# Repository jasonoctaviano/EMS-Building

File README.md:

# EMS-Building
Energy monitoring system for house or building using mbed

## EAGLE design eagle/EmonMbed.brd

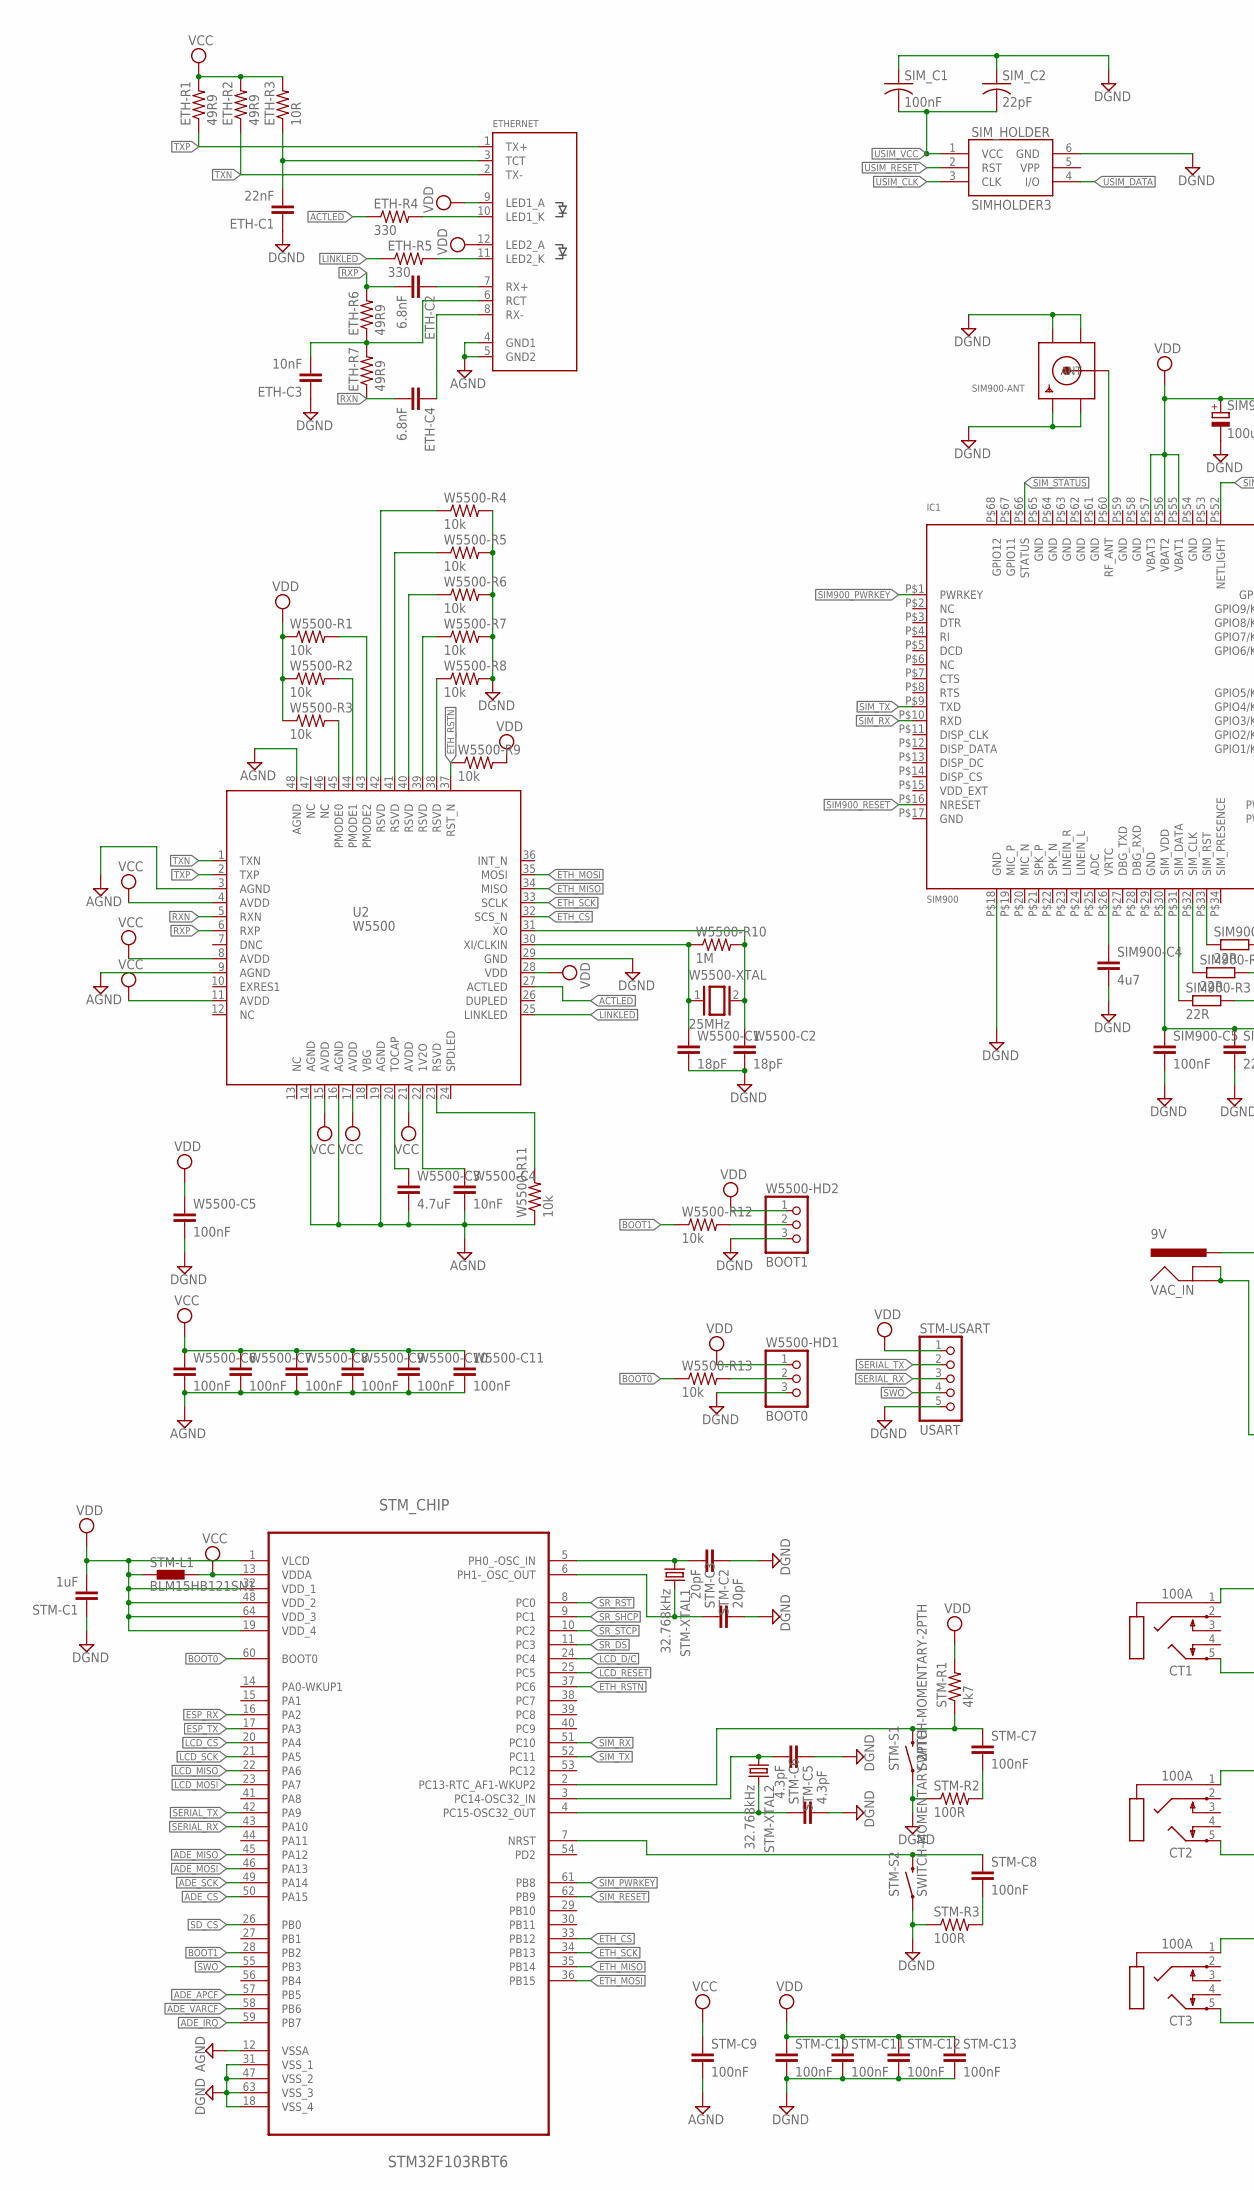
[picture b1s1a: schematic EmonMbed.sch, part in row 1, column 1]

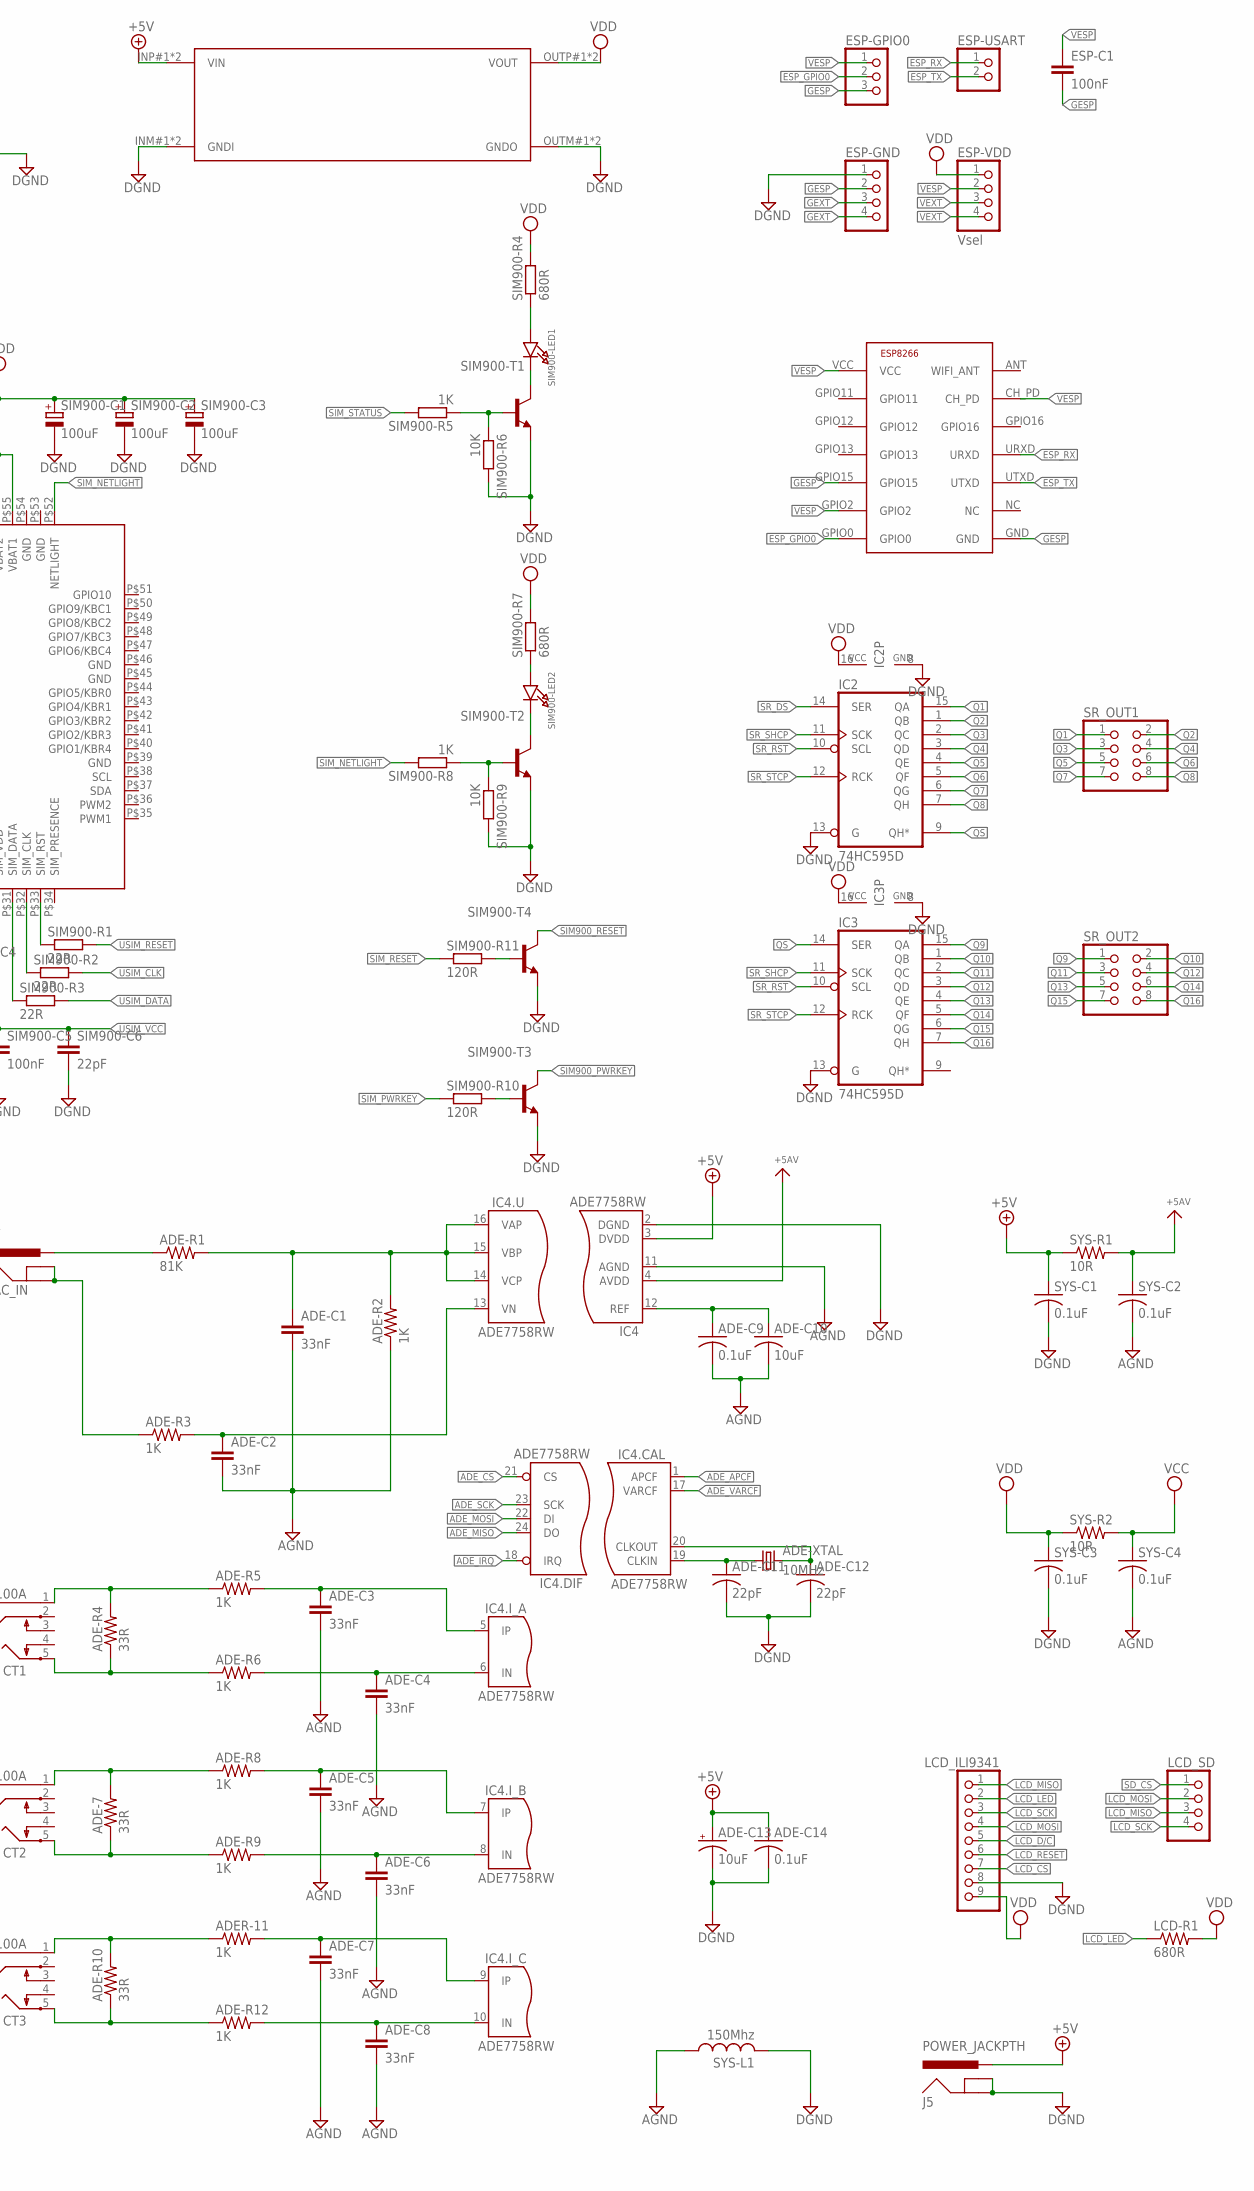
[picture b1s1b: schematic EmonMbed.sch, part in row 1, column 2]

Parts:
ADE-7: 33R; 0603-RES
ADE-C1, ADE-C2, ADE-C3, ADE-C4, ADE-C5, ADE-C6, ADE-C7, ADE-C8: 33nF; 0603-CAP
ADE-C9: 0.1uF; C0805K
ADE-C10: 10uF; C0805K
ADE-C11, ADE-C12: 22pF; C0805K
ADE-C13: 10uF; C/6032-28R
ADE-C14: 0.1uF; C0805
ADE-R1: 81K; 0603-RES
ADE-R2, ADE-R3, ADE-R5, ADE-R6, ADE-R8, ADE-R9, ADE-R12: 1K; 0603-RES
ADE-R4, ADE-R10: 33R; 0603-RES
ADE-XTAL: 10MHz; HC49US
ADER-11: 1K; 0603-RES
CT1, CT2, CT3: 100A; STX3100
DCDC-3.5V: DCDCMODULE_SMALL; DCDCMODULE-SMALL
ESP8266: ESP-07
ESP-C1: 100nF; C0603
ESP-GND: PINHD-1X4; 1X04
ESP-GPIO0: PINHD-1X3; 1X03
ESP-USART: PINHD-1X2; 1X02
ESP-VDD: Vsel; 1X04
ETH-C1: 22nF; C0603
ETH-C2, ETH-C4: 6.8nF; C0603
ETH-C3: 10nF; C0603
ETH-R1, ETH-R2, ETH-R6, ETH-R7: 49R9; R0603
ETH-R3: 10R; R0603
ETH-R4, ETH-R5: 330; R0603
ETHERNET: RJ45J0026D21BNL; RJ45_PULSEJACK
IC1: SIM900; SIM900_SMT
IC2, IC3: 74HC595D; SO16
IC4: ADE7758RW; SOIC24
J5: POWER_JACKPTH; POWER_JACK_PTH
LCD-R1: 680R; 0603-RES
LCD_ILI9341: PINHD-1X9; 1X09
LCD_SD: PINHD-1X4; 1X04
SIM900-ANT: SMACONNECTOR; SMA90_DIP
SIM900-C1, SIM900-C2, SIM900-C3: 100uF; 153CLV-0605
SIM900-C4: 4u7; C0603
SIM900-C5: 100nF; C0603
SIM900-C6: 22pF; C0603
SIM900-LED1, SIM900-LED2: LED0805_NOOUTLINE; CHIPLED_0805_NOOUTLINE
SIM900-R1, SIM900-R2, SIM900-R3: 22R; R0603
SIM900-R4, SIM900-R7: 680R; R0603
SIM900-R5, SIM900-R8: 1K; R0603
SIM900-R6, SIM900-R9: 10K; R0603
SIM900-R10, SIM900-R11: 120R; R0603
SIM900-T1, SIM900-T2, SIM900-T3, SIM900-T4: MMBT2222ALT1-NPN-SOT23-BEC; SOT23-BEC
SIM_C1: 100nF; C0603K
SIM_C2: 22pF; C0603K
SIM_HOLDER: SIMHOLDER3
SR_OUT1, SR_OUT2: PINHD-2X4/90; 2X04/90
STM-C1: 1uF; C0603
STM-C2, STM-C3: 20pF; C0603
STM-C5, STM-C6: 4.3pF; C0603
STM-C7, STM-C8, STM-C9, STM-C10, STM-C11, STM-C12, STM-C13: 100nF; C0603
STM-L1: BLM15HB121SN1; 0402
STM-R1: 4k7; R0603
STM-R2, STM-R3: 100R; R0603
STM-S1, STM-S2: SWITCH-MOMENTARY-2PTH; TACTILE-PTH
STM-USART: USART; 1X05
STM-XTAL1, STM-XTAL2: 32.768kHz; TC26H
STM_CHIP: STM32F103RBT6; QFP50P1200X1200X160-64N
SYS-C1, SYS-C2, SYS-C3, SYS-C4: 0.1uF; C0805
SYS-L1: 150Mhz; POWER-CHOKE_WE-TPC
SYS-R1, SYS-R2: 10R; 0603-RES
U2: W5500
VAC_IN: 9V; POWER_JACK_PTH
W5500-C1, W5500-C2: 18pF; C0603
W5500-C3: 4.7uF; C0603
W5500-C4: 10nF; C0603
W5500-C5, W5500-C6, W5500-C7, W5500-C8, W5500-C9, W5500-C10, W5500-C11: 100nF; C0603
W5500-HD1: BOOT0; 1X03
W5500-HD2: BOOT1; 1X03
W5500-R1, W5500-R2, W5500-R3, W5500-R4, W5500-R5, W5500-R6, W5500-R7, W5500-R8, W5500-R9, W5500-R11, W5500-R12, W5500-R13: 10k; R0603
W5500-R10: 1M; R0603
W5500-XTAL: 25MHz; QS

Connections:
+5V: ADE-C13.+, ADE-C14.1, DCDC-3.5V.INP#1 (VIN), DCDC-3.5V.INP#2 (VIN), IC4.3 (DVDD), J5.PWR, SYS-C1.1, SYS-R1.1
ACTLED: ETH-R4.1, U2.27 (ACTLED)
ADE_APCF: IC4.1 (APCF), STM_CHIP.57 (PB5)
ADE_CS: IC4.21 (CS), STM_CHIP.50 (PA15)
ADE_IRQ: IC4.18 (IRQ), STM_CHIP.59 (PB7)
ADE_MISO: IC4.24 (DO), STM_CHIP.45 (PA12)
ADE_MOSI: IC4.22 (DI), STM_CHIP.46 (PA13)
ADE_SCK: IC4.23 (SCK), STM_CHIP.49 (PA14)
ADE_VARCF: IC4.17 (VARCF), STM_CHIP.58 (PB6)
AGND: ADE-C1.2, ADE-C2.2, ADE-C3.2, ADE-C4.2, ADE-C5.2, ADE-C6.2, ADE-C7.2, ADE-C8.2, ADE-C9.2, ADE-C10.2, ADE-R2.1, ETHERNET.4 (GND1), ETHERNET.5 (GND2), IC4.11 (AGND), STM-C9.2, STM_CHIP.12 (VSSA), SYS-C2.2, SYS-C4.2, SYS-L1.1, U2.3 (AGND), U2.9 (AGND), U2.14 (AGND), U2.16 (AGND), U2.19 (AGND), U2.48 (AGND), W5500-C3.2, W5500-C4.2, W5500-C6.2, W5500-C7.2, W5500-C8.2, W5500-C9.2, W5500-C10.2, W5500-C11.2, W5500-R11.1
AVDD: IC4.4 (AVDD), SYS-C2.1, SYS-R1.2
BOOT0: STM_CHIP.60 (BOOT0), W5500-R13.1
BOOT1: STM_CHIP.28 (PB2), W5500-R12.1
DGND: ADE-C11.2, ADE-C12.2, ADE-C13.-, ADE-C14.2, DCDC-3.5V.INM#1 (GNDI), DCDC-3.5V.INM#2 (GNDI), DCDC-3.5V.OUTM#1 (GNDO), DCDC-3.5V.OUTM#2 (GNDO), ESP-GND.1, ETH-C1.1, ETH-C3.1, IC1.P$18 (GND), IC2.8 (GND), IC2.13 (G), IC3.8 (GND), IC3.13 (G), IC4.2 (DGND), J5.GND, J5.GNDBREAK, LCD_ILI9341.8, SIM900-ANT.GND1, SIM900-ANT.GND2, SIM900-ANT.GND3, SIM900-ANT.GND4, SIM900-C1.-, SIM900-C2.-, SIM900-C3.-, SIM900-C4.2, SIM900-C5.2, SIM900-C6.2, SIM900-R6.2, SIM900-R9.2, SIM900-T1.E, SIM900-T2.E, SIM900-T3.E, SIM900-T4.E, SIM_C1.1, SIM_C2.1, SIM_HOLDER.6 (GND), STM-C1.1, STM-C2.1, STM-C3.2, STM-C5.1, STM-C6.2, STM-C10.2, STM-C11.2, STM-C12.2, STM-C13.2, STM-R2.1, STM-R3.1, STM-S1.1, STM-S2.1, STM-USART.5, STM_CHIP.18 (VSS_4), STM_CHIP.31 (VSS_1), STM_CHIP.47 (VSS_2), STM_CHIP.63 (VSS_3), SYS-C1.2, SYS-C3.2, SYS-L1.2, U2.29 (GND), W5500-C1.2, W5500-C2.2, W5500-C5.2, W5500-HD1.3, W5500-HD2.3, W5500-R4.2, W5500-R5.2, W5500-R6.2, W5500-R7.2, W5500-R8.2
ESP_GPIO0: ESP8266.GPIO0, ESP-GPIO0.2
ESP_RX: ESP8266.URXD, ESP-USART.1, STM_CHIP.16 (PA2)
ESP_TX: ESP8266.UTXD, ESP-USART.2, STM_CHIP.17 (PA3)
ETH_CS: STM_CHIP.33 (PB12), U2.32 (SCS_N)
ETH_MISO: STM_CHIP.35 (PB14), U2.34 (MISO)
ETH_MOSI: STM_CHIP.36 (PB15), U2.35 (MOSI)
ETH_RSTN: STM_CHIP.37 (PC6), U2.37 (RST_N), W5500-R9.1
ETH_SCK: STM_CHIP.34 (PB13), U2.33 (SCLK)
GESP: ESP8266.GND, ESP8266.GPIO15, ESP-C1.2, ESP-GND.2, ESP-GPIO0.3
GEXT: ESP-GND.3, ESP-GND.4
GND: IC1.P$17 (GND), IC1.P$29 (GND), IC1.P$39 (GND), IC1.P$45 (GND), IC1.P$46 (GND), IC1.P$53 (GND), IC1.P$54 (GND), IC1.P$58 (GND), IC1.P$59 (GND), IC1.P$61 (GND), IC1.P$62 (GND), IC1.P$63 (GND), IC1.P$64 (GND), IC1.P$65 (GND)
GPIO11: IC1.P$67 (GPIO11)
GPIO12: IC1.P$68 (GPIO12)
IBN: ADE-7.1, ADE-R9.1, CT2.5
ICN: ADE-R10.1, ADE-R12.1, CT3.5
LCD_CS: LCD_ILI9341.7, STM_CHIP.20 (PA4)
LCD_D/C: LCD_ILI9341.5, STM_CHIP.24 (PC4)
LCD_LED: LCD-R1.1, LCD_ILI9341.2
LCD_MISO: LCD_ILI9341.1, LCD_SD.3, STM_CHIP.22 (PA6)
LCD_MOSI: LCD_ILI9341.4, LCD_SD.2, STM_CHIP.23 (PA7)
LCD_RESET: LCD_ILI9341.6, STM_CHIP.25 (PC5)
LCD_SCK: LCD_ILI9341.3, LCD_SD.4, STM_CHIP.21 (PA5)
LINKLED: ETH-R5.1, U2.25 (LINKLED)
unnamed: STM-C5.2, STM-XTAL2.1, STM_CHIP.3 (PC14-OSC32_IN)
unnamed: STM-C6.1, STM-XTAL2.2, STM_CHIP.4 (PC15-OSC32_OUT)
unnamed: IC1.P$31 (SIM_DATA), SIM900-R3.1
unnamed: STM-C7.1, STM-R1.1, STM-S1.3 (2), STM_CHIP.2 (PC13-RTC_AF1-WKUP2)
unnamed: STM-C7.2, STM-R2.2
unnamed: STM-C2.2, STM-XTAL1.1, STM_CHIP.5 (PH0_-OSC_IN)
unnamed: STM-C3.1, STM-XTAL1.2, STM_CHIP.6 (PH1-_OSC_OUT)
unnamed: IC1.P$32 (SIM_CLK), SIM900-R2.1
unnamed: STM-C8.2, STM-R3.2
unnamed: ETH-R4.2, ETHERNET.10 (LED1_K)
unnamed: ETH-R5.2, ETHERNET.11 (LED2_K)
unnamed: IC1.P$33 (SIM_RST), SIM900-R1.1
unnamed: IC1.P$26 (VRTC), SIM900-C4.1
unnamed: IC1.P$60 (RF_ANT), SIM900-ANT.ANTENNA (ANT)
unnamed: SIM900-LED1.A, SIM900-R4.1
unnamed: SIM900-LED1.C, SIM900-T1.C
unnamed: SIM900-R5.1, SIM900-R6.1, SIM900-T1.B
unnamed: SIM900-LED2.A, SIM900-R7.1
unnamed: SIM900-LED2.C, SIM900-T2.C
unnamed: SIM900-R8.1, SIM900-R9.1, SIM900-T2.B
unnamed: ETH-C2.1, ETHERNET.7 (RX+)
unnamed: ETH-C1.2, ETH-R3.1, ETHERNET.3 (TCT)
unnamed: ADE-C7.1, ADER-11.2, IC4.9 (IP)
unnamed: ADE-7.2, ADE-R8.1, CT2.1
unnamed: ETH-C4.1, ETHERNET.8 (RX-)
unnamed: ADE-C3.1, ADE-R5.2, IC4.5 (IP)
unnamed: ADE-C4.1, ADE-R6.2, IC4.6 (IN)
unnamed: ETH-C3.2, ETH-R6.1, ETH-R7.2, ETHERNET.6 (RCT)
unnamed: ADE-C6.1, ADE-R9.2, IC4.8 (IN)
unnamed: ADE-C5.1, ADE-R8.2, IC4.7 (IP)
unnamed: ADE-C9.1, ADE-C10.1, IC4.12 (REF)
unnamed: ADE-C11.1, ADE-XTAL.1, IC4.19 (CLKIN)
unnamed: ADE-C12.1, ADE-XTAL.2, IC4.20 (CLKOUT)
unnamed: ADE-C2.1, ADE-R3.2, IC4.13 (VN)
unnamed: ADE-R1.1, VAC_IN.PWR
unnamed: ADE-C1.1, ADE-R1.2, ADE-R2.2, IC4.14 (VCP), IC4.15 (VBP), IC4.16 (VAP)
unnamed: U2.20 (TOCAP), W5500-C3.1
unnamed: ADE-R4.2, ADE-R5.1, CT1.1
unnamed: ADE-C8.1, ADE-R12.2, IC4.10 (IN)
unnamed: U2.22 (1V2O), W5500-C4.1
unnamed: U2.23 (RSVD), W5500-R11.2
unnamed: W5500-HD1.2, W5500-R13.2
unnamed: SIM900-R10.2, SIM900-T3.B
unnamed: SIM900-R11.2, SIM900-T4.B
unnamed: W5500-HD2.2, W5500-R12.2
unnamed: ADE-R4.1, ADE-R6.1, CT1.5
unnamed: ADE-R10.2, ADER-11.1, CT3.1
unnamed: U2.30 (XI/CLKIN), W5500-C1.1, W5500-R10.1, W5500-XTAL.1
unnamed: U2.31 (XO), W5500-C2.1, W5500-R10.2, W5500-XTAL.2
unnamed: ADE-R3.1, VAC_IN.GND, VAC_IN.GNDBREAK
unnamed: U2.38 (RSVD), W5500-R8.1
unnamed: U2.39 (RSVD), W5500-R7.1
unnamed: U2.40 (RSVD), W5500-R6.1
unnamed: U2.41 (RSVD), W5500-R5.1
unnamed: U2.42 (RSVD), W5500-R4.1
unnamed: U2.43 (PMODE2), W5500-R1.2
unnamed: U2.44 (PMODE1), W5500-R2.2
unnamed: U2.45 (PMODE0), W5500-R3.2
NRST: STM-C8.1, STM-S2.3 (2), STM_CHIP.7 (NRST)
Q1: IC2.15 (QA), SR_OUT1.1
Q2: IC2.1 (QB), SR_OUT1.2
Q3: IC2.2 (QC), SR_OUT1.3
Q4: IC2.3 (QD), SR_OUT1.4
Q5: IC2.4 (QE), SR_OUT1.5
Q6: IC2.5 (QF), SR_OUT1.6
Q7: IC2.6 (QG), SR_OUT1.7
Q8: IC2.7 (QH), SR_OUT1.8
Q9: IC3.15 (QA), SR_OUT2.1
Q10: IC3.1 (QB), SR_OUT2.2
Q11: IC3.2 (QC), SR_OUT2.3
Q12: IC3.3 (QD), SR_OUT2.4
Q13: IC3.4 (QE), SR_OUT2.5
Q14: IC3.5 (QF), SR_OUT2.6
Q15: IC3.6 (QG), SR_OUT2.7
Q16: IC3.7 (QH), SR_OUT2.8
QS: IC2.9 (QH*), IC3.14 (SER)
RXN: ETH-C4.2, ETH-R7.1, U2.5 (RXN)
RXP: ETH-C2.2, ETH-R6.2, U2.6 (RXP)
SD_CS: LCD_SD.1, STM_CHIP.26 (PB0)
SERIAL_RX: STM-USART.3, STM_CHIP.43 (PA10)
SERIAL_TX: STM-USART.2, STM_CHIP.42 (PA9)
SIM900_PWRKEY: IC1.P$1 (PWRKEY), SIM900-T3.C
SIM900_RESET: IC1.P$16 (NRESET), SIM900-T4.C
SIM_NETLIGHT: IC1.P$52 (NETLIGHT), SIM900-R8.2
SIM_PWRKEY: SIM900-R10.1, STM_CHIP.61 (PB8)
SIM_RESET: SIM900-R11.1, STM_CHIP.62 (PB9)
SIM_RX: IC1.P$10 (RXD), STM_CHIP.51 (PC10)
SIM_STATUS: IC1.P$66 (STATUS), SIM900-R5.2
SIM_TX: IC1.P$9 (TXD), STM_CHIP.52 (PC11)
SR_DS: IC2.14 (SER), STM_CHIP.11 (PC3)
SR_RST: IC2.10 (SCL), IC3.10 (SCL), STM_CHIP.8 (PC0)
SR_SHCP: IC2.11 (SCK), IC3.11 (SCK), STM_CHIP.9 (PC1)
SR_STCP: IC2.12 (RCK), IC3.12 (RCK), STM_CHIP.10 (PC2)
SWO: STM-USART.4, STM_CHIP.55 (PB3)
TXN: ETH-R2.1, ETHERNET.2 (TX-), U2.1 (TXN)
TXP: ETH-R1.1, ETHERNET.1 (TX+), U2.2 (TXP)
USIM_CLK: SIM900-R2.2, SIM_HOLDER.3 (CLK)
USIM_DATA: SIM900-R3.2, SIM_HOLDER.4 (I/O)
USIM_RESET: SIM900-R1.2, SIM_HOLDER.2 (RST)
USIM_VCC: IC1.P$30 (SIM_VDD), SIM900-C5.1, SIM900-C6.1, SIM_C1.2, SIM_C2.2, SIM_HOLDER.1 (VCC)
VCC: ETH-R1.2, ETH-R2.2, ETH-R3.2, STM-C9.1, STM-L1.2, STM_CHIP.13 (VDDA), SYS-C4.1, SYS-R2.2, U2.4 (AVDD), U2.8 (AVDD), U2.11 (AVDD), U2.15 (AVDD), U2.17 (AVDD), U2.21 (AVDD), W5500-C6.1, W5500-C7.1, W5500-C8.1, W5500-C9.1, W5500-C10.1, W5500-C11.1
VDD: DCDC-3.5V.OUTP#1 (VOUT), DCDC-3.5V.OUTP#2 (VOUT), ESP-VDD.1, ETHERNET.9 (LED1_A), ETHERNET.12 (LED2_A), IC1.P$55 (VBAT1), IC1.P$56 (VBAT2), IC1.P$57 (VBAT3), IC2.16 (VCC), IC3.16 (VCC), LCD-R1.2, LCD_ILI9341.9, SIM900-C1.+, SIM900-C2.+, SIM900-C3.+, SIM900-R4.2, SIM900-R7.2, STM-C1.2, STM-C10.1, STM-C11.1, STM-C12.1, STM-C13.1, STM-L1.1, STM-R1.2, STM-USART.1, STM_CHIP.1 (VLCD), STM_CHIP.19 (VDD_4), STM_CHIP.32 (VDD_1), STM_CHIP.48 (VDD_2), STM_CHIP.64 (VDD_3), SYS-C3.1, SYS-R2.1, U2.28 (VDD), W5500-C5.1, W5500-HD1.1, W5500-HD2.1, W5500-R1.1, W5500-R2.1, W5500-R3.1, W5500-R9.2
VESP: ESP8266.CH_PD, ESP8266.GPIO2, ESP8266.VCC, ESP-C1.1, ESP-GPIO0.1, ESP-VDD.2
VEXT: ESP-VDD.3, ESP-VDD.4

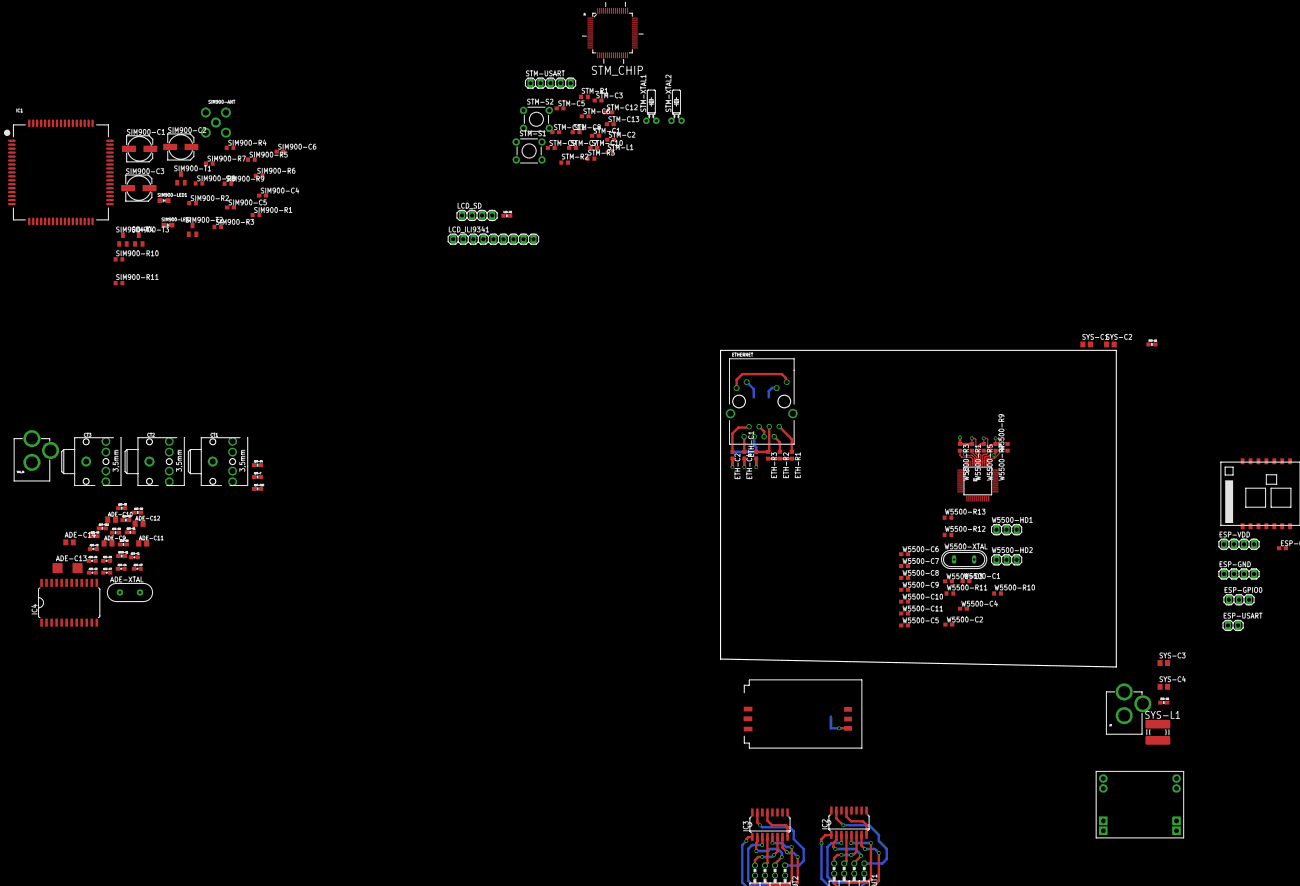
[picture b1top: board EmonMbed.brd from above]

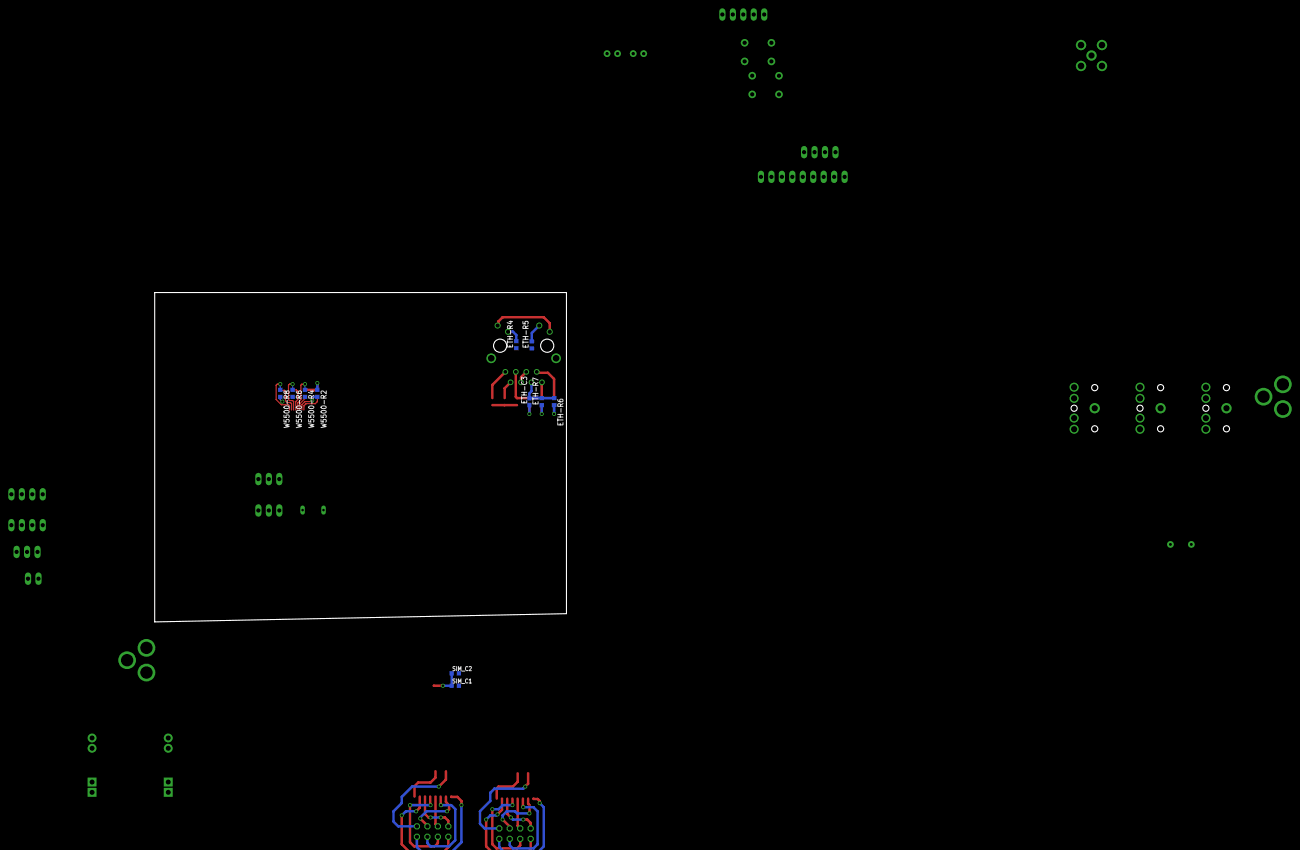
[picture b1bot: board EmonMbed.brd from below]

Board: 2 copper layers, 100.0 x 80.0 mm, 144 parts (11 on the bottom side), 139 nets.

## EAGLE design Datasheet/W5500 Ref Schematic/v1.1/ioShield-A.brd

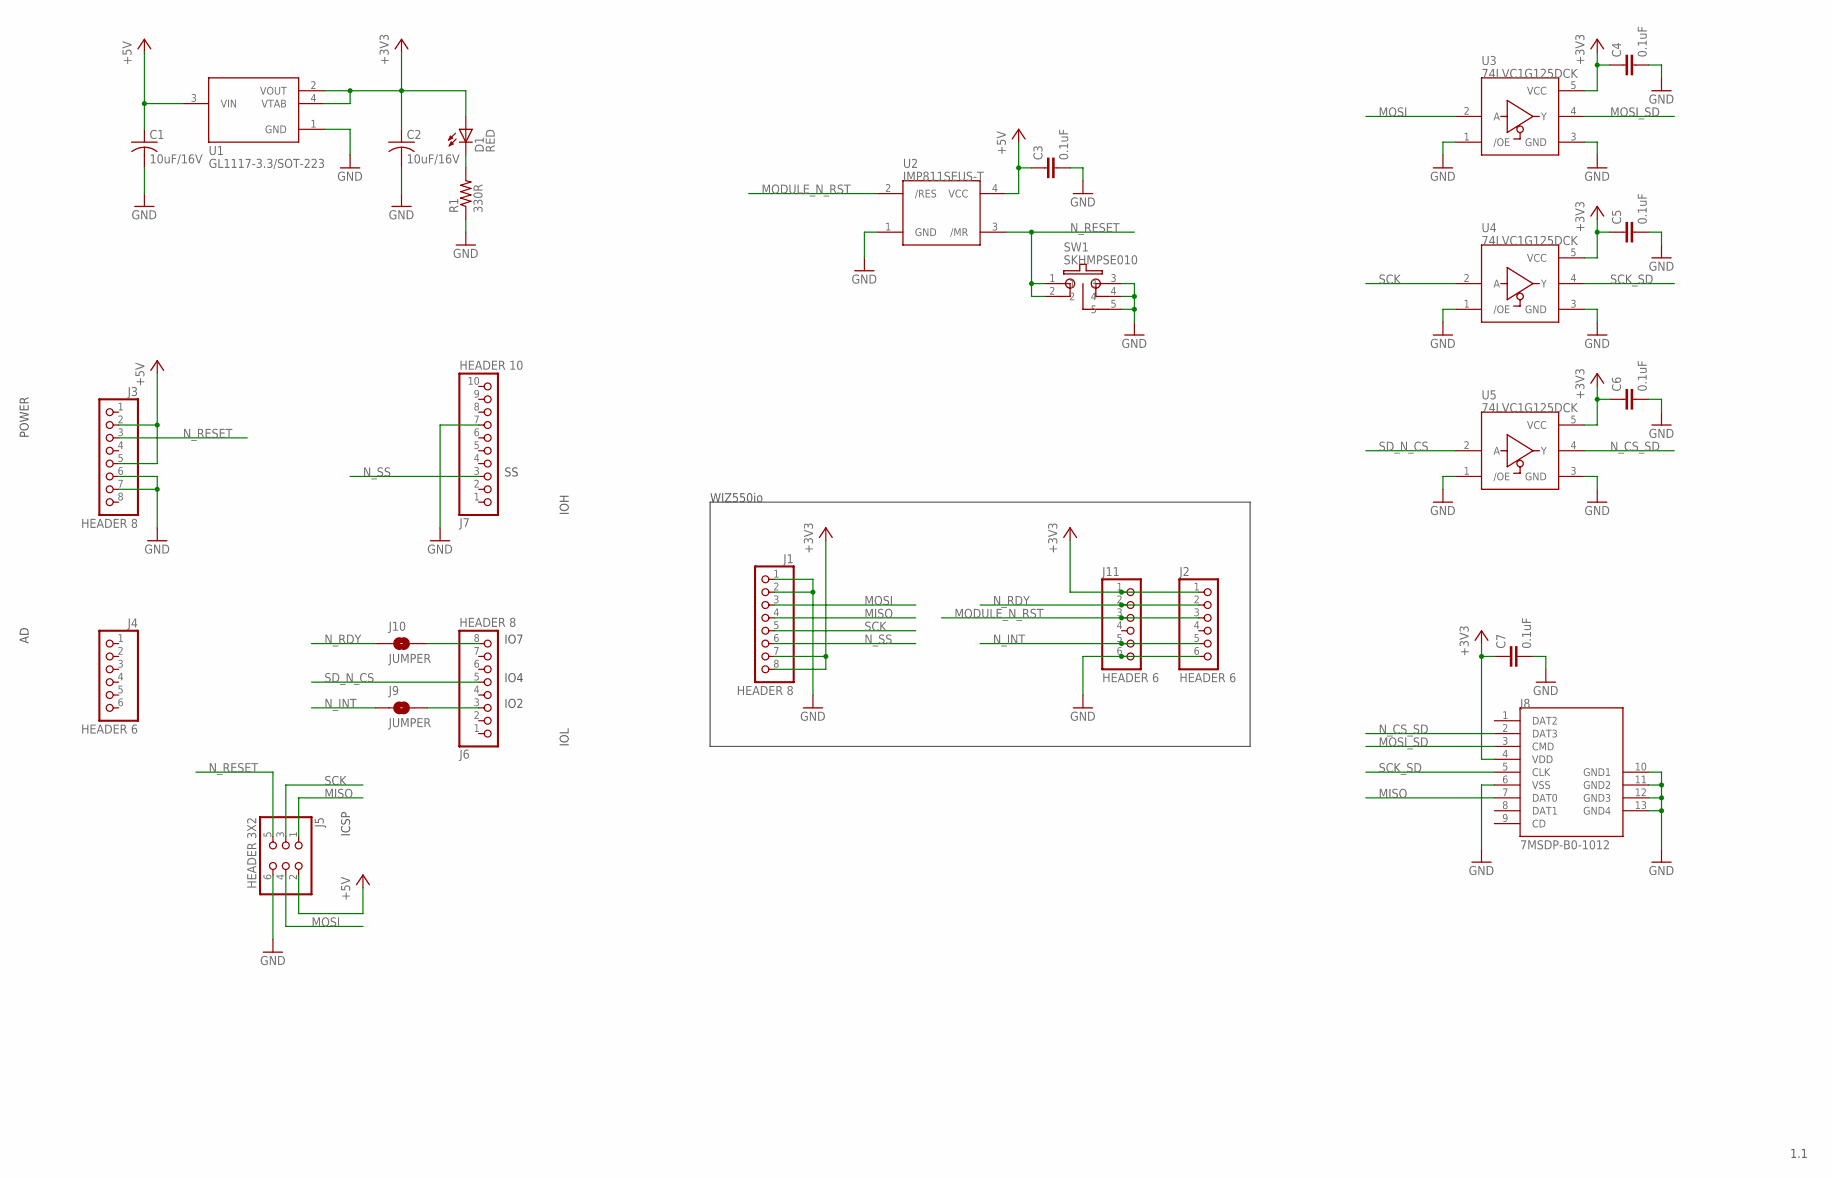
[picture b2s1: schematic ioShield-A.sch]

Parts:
C1, C2: 10uF/16V; CT-A(3216)
C3, C4, C5, C6, C7: 0.1uF; C1608
D1: RED; CHIP-LED1608
J1, J3, J6: HEADER 8; HEADER1X8
J2, J4, J11: HEADER 6; HEADER1X6
J5: HEADER 3X2; HEADER3X2
J7: HEADER 10; HEADER1X10
J8: 7MSDP-B0-1012; MICROSD_HC
J9, J10: JUMPER; SJ
R1: 330R; R1608
SW1: SKHMPSE010; TACT_6.2X6.5
U1: GL1117-3.3/SOT-223; SOT223_HC
U2: IMP811SEUS-T; SOT-143
U3, U4, U5: 74LVC1G125DCK; SC70-5(DCK)

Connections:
+3V3: C2.+ (1), C4.1, C5.1, C6.1, C7.1, D1.A, J1.7, J1.8, J2.1, J8.4 (VDD), J11.1, U1.2 (VOUT), U1.4 (VTAB), U3.5 (VCC), U4.5 (VCC), U5.5 (VCC)
+5V: C1.+ (1), C3.1, J3.2, J3.5, J5.2, U1.3 (VIN), U2.4 (VCC)
GND: C1.- (2), C2.- (2), C3.2, C4.2, C5.2, C6.2, C7.2, J1.1, J1.2, J2.6, J3.6, J3.7, J5.6, J7.7, J8.6 (VSS), J8.10 (GND1), J8.11 (GND2), J8.12 (GND3), J8.13 (GND4), J11.6, R1.1, SW1.3, SW1.4, SW1.5, U1.1 (GND), U2.1 (GND), U3.1 (/OE), U3.3 (GND), U4.1 (/OE), U4.3 (GND), U5.1 (/OE), U5.3 (GND)
MISO: J1.4, J5.1, J8.7 (DAT0)
MODULE_N_RST: J2.3, J11.3, U2.2 (/RES)
MOSI: J1.3, J5.4, U3.2 (A)
MOSI_SD: J8.3 (CMD), U3.4 (Y)
unnamed: D1.C, R1.2
unnamed: J6.8, J10.2
unnamed: J6.3, J9.2
N_CS_SD: J8.2 (DAT3), U5.4 (Y)
N_INT: J2.5, J9.1, J11.5
N_RDY: J2.2, J10.1, J11.2
N_RESET: J3.3, J5.5, SW1.1, SW1.2, U2.3 (/MR)
N_SS: J1.6, J7.3
SCK: J1.5, J5.3, U4.2 (A)
SCK_SD: J8.5 (CLK), U4.4 (Y)
SD_N_CS: J6.5, U5.2 (A)

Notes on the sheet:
IO7
IO4
IO2
WIZ550io
POWER
IOL
IOH
ICSP
1.1

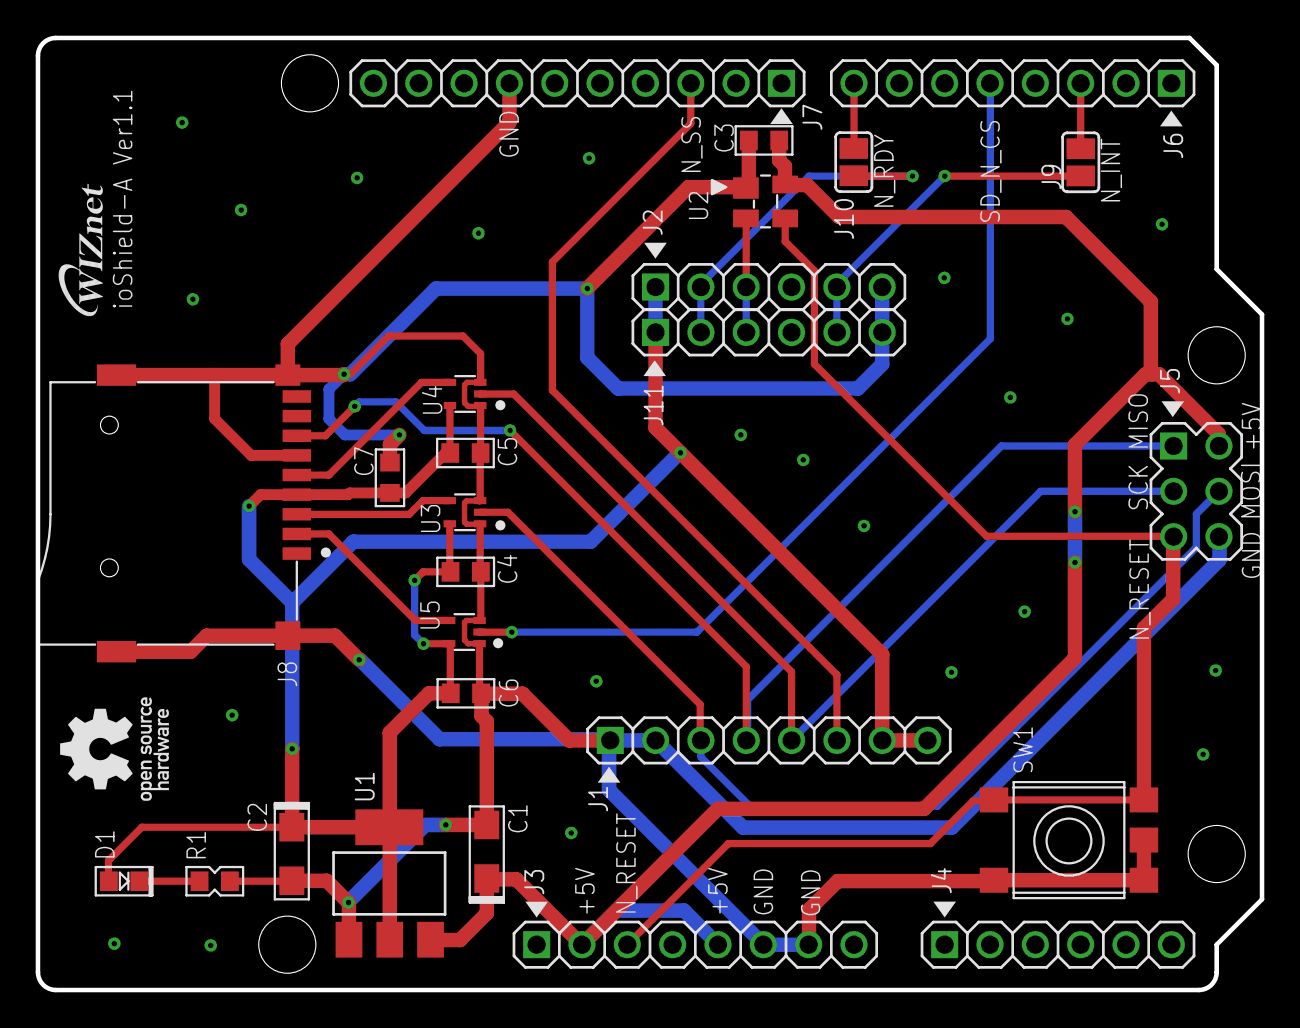
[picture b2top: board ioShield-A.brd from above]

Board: 2 copper layers, 68.6 x 53.3 mm, 28 parts (0 on the bottom side), 18 nets.

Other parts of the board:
E$1: OSH800_DOT-DCALE-0.3MIL
U$1: WIZNET_DOT-SCALE-0.1MIL

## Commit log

2015-02-26 Adding datasheet and schematic reference
2015-02-26 Eagle schematic and board design
2015-03-03 new schematics and datasheet
2015-03-03 update schematic
2015-03-09 Updated Final Schematics

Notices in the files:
parts and their libraries:
SparkFun-Passives: Licensing: CC v3.0 Share-Alike You are welcome to use this library for commercial purposes.
microbuilder: This work is placed in the public domain, and may be freely used for commercial and non-commercial work with the following conditions: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
